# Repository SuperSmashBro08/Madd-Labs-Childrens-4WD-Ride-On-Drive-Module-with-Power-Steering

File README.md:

# Kids Ride-On Framework

An open-source framework for building smart, connected kids' ride-on vehicles with OTA (Over-The-Air) firmware updates, web-based control, and modular peripheral support.

---

## 🎯 Project Overview

This project provides a complete hardware and software framework for upgrading kids' electric ride-on toys with:

- **Dual-MCU Architecture**: ESP32-S3 for WiFi/Web + Teensy 4.1 for real-time control
- **OTA Firmware Updates**: Update both MCUs wirelessly via web browser
- **Web Dashboard**: Monitor and control the vehicle from any device
- **Modular Design**: Easy to add motors, LEDs, sensors, and more
- **Custom PCB**: Purpose-built circuit board for clean integration

---

## 📁 Project Structure

```
Kids-Ride-On-Framework/
├── esp32_flasher/           # ESP32-S3 firmware (WiFi, Web Server, OTA)
│   ├── esp32_flasher.ino    # Main ESP32 code
│   ├── secrets.h.example    # Template for WiFi credentials
│   └── README.md            # ESP32-specific documentation
│
├── teensy_flasherx/         # Teensy 4.1 firmware (Motor control, sensors)
│   ├── teensy_flasherx.ino  # Main application code (YOUR CODE HERE)
│   ├── FlasherXOTA.h/cpp    # OTA update handler (don't modify)
│   ├── FXUtil.h/cpp         # Intel HEX parser (don't modify)
│   ├── FlashTxx.h/c         # Flash primitives (don't modify)
│   └── README.md            # Teensy-specific documentation
│
├── hardware/                # Hardware design files
│   └── PCB/
│       └── Kids Ride On 2.1/
│           ├── Kicad files/ # KiCad schematic and PCB
│           ├── bom/         # Bill of materials
│           ├── 3d/          # 3D models
│           └── Production/  # Gerber files for manufacturing
│
├── Backup/                  # Backup of original firmware
├── readme files/            # Additional documentation
├── .gitignore               # Git ignore rules
└── README.md                # This file
```

---

## 🚀 Getting Started

### Prerequisites

- [Arduino IDE 2.x](https://www.arduino.cc/en/software) or [PlatformIO](https://platformio.org/)
- [Teensyduino](https://www.pjrc.com/teensy/teensyduino.html) add-on for Arduino IDE
- ESP32 Arduino Core (install via Board Manager)

### Hardware Required

- ESP32-S3 DevKitC (or compatible)
- Teensy 4.1
- Custom PCB (see `hardware/PCB/`) or breadboard setup
- 12V/24V power supply (depending on your motors)
- Motors, sensors, LEDs as needed

### Quick Start

1. **Clone the repository**
   ```bash
   git clone https://github.com/yourusername/kids-ride-on-framework.git
   cd kids-ride-on-framework
   ```

2. **Configure WiFi credentials**
   ```bash
   cd esp32_flasher
   cp secrets.h.example secrets.h
   # Edit secrets.h with your WiFi SSID and password
   ```

3. **Upload ESP32 firmware**
   - Open `esp32_flasher/esp32_flasher.ino` in Arduino IDE
   - Select board: ESP32-S3 Dev Module
   - Upload via USB
   - Open Serial Monitor to see the assigned IP address

4. **Upload Teensy firmware**
   - Open `teensy_flasherx/teensy_flasherx.ino` in Arduino IDE
   - Select board: Teensy 4.1
   - Upload via USB (first time only - then use OTA!)

5. **Access the Web Dashboard**
   - Open your browser to the IP address shown in Serial Monitor
   - You can now upload firmware updates wirelessly!

---

## ⚙️ Configuration

### Sensor Calibration (IMPORTANT!)

Every vehicle will have different sensor ranges. Open `teensy_flasherx/teensy_flasherx.ino` and find the **USER CONFIGURATION SECTION** near the top:

```cpp
//******************************************************************************
//                    USER CONFIGURATION SECTION
//******************************************************************************

// ----- STEERING 1 (Primary/Front) -----
#define STEERING1_PIN         A0      // Analog input pin
#define STEERING1_MIN         0       // Raw ADC at full LEFT
#define STEERING1_MAX         1023    // Raw ADC at full RIGHT
#define STEERING1_CENTER      512     // Raw ADC at CENTER

// ----- THROTTLE 1 (Primary) -----
#define THROTTLE1_PIN         A2      // Analog input pin
#define THROTTLE1_MIN         100     // Raw ADC at NO throttle
#define THROTTLE1_MAX         900     // Raw ADC at FULL throttle

// ... more configuration options
```

**How to calibrate:**
1. Upload the firmware with default values
2. Open Serial Monitor
3. Move your steering/throttle and note the raw ADC values
4. Update the MIN/MAX/CENTER values in the code
5. Re-upload (via OTA!)

### WiFi Configuration

For security, WiFi credentials are stored in `secrets.h` which is **not committed to git**.

1. Copy the example file:
   ```bash
   cp esp32_flasher/secrets.h.example esp32_flasher/secrets.h
   ```

2. Edit `secrets.h` with your credentials:
   ```cpp
   #define WIFI_SSID     "YourWiFiName"
   #define WIFI_PASSWORD "YourWiFiPassword"
   ```

---

## 🔧 Hardware

### PCB Design

The custom PCB connects the ESP32-S3 and Teensy 4.1 with proper level shifting and power regulation. Design files are in `hardware/PCB/Kids Ride On 2.1/`.

### Complete Pinout (V2.1 PCB)

#### Teensy 4.1 Pinout

**Analog Inputs (0–3.3V)**
| Pin | Function | Description |
|-----|----------|-------------|
| 17 (A3) | S1_WIPER | Steering Potentiometer |
| 23 (A9) | T1_WIPER | Throttle Potentiometer |
| 16 (A2) | AS5600_OUT | Magnetic Encoder Analog |
| 24 (A10) | STEER_I_L | Steering Motor Current Left |
| 25 (A11) | STEER_I_R | Steering Motor Current Right |
| 26 (A12) | FRONT_I_L | Front Drive Current Left |
| 27 (A13) | FRONT_I_R | Front Drive Current Right |
| 38 (A14) | REAR_I_L | Rear Drive Current Left |
| 39 (A15) | REAR_I_R | Rear Drive Current Right |

**Digital Inputs (3.3V Logic)**
| Pin | Function | Description |
|-----|----------|-------------|
| 28 | SHIFT_FWD | Shifter Forward |
| 29 | SHIFT_REV | Shifter Reverse |
| 30 | MODE_SEL | Mode Select |
| 31 | E_BRAKE | E-Brake Input |

**PWM Outputs (3.3V)**
| Pin | Function | Description |
|-----|----------|-------------|
| 2 | STEER_LPWM | Steering Left PWM |
| 3 | STEER_RPWM | Steering Right PWM |
| 6 | FRONT_LPWM | Front Drive Left PWM |
| 9 | FRONT_RPWM | Front Drive Right PWM |
| 12 | REAR_LPWM | Rear Drive Left PWM |
| 13 | REAR_RPWM | Rear Drive Right PWM |

**Motor Driver Enable (3.3V → 5V via level shifter)**
| Pin | Function | Description |
|-----|----------|-------------|
| 4 | STEER_L_EN | Steering Left Enable |
| 5 | STEER_R_EN | Steering Right Enable |
| 10 | FRONT_L_EN | Front Drive Left Enable |
| 11 | FRONT_R_EN | Front Drive Right Enable |
| 32 | REAR_L_EN | Rear Drive Left Enable |
| 33 | REAR_R_EN | Rear Drive Right Enable |

**I2C (AS5600 Encoder)**
| Pin | Function |
|-----|----------|
| 18 | SDA |
| 19 | SCL |

**UART to ESP32-S3**
| Teensy Pin | ESP32 Pin | Function |
|------------|-----------|----------|
| 7 (RX2) | GPIO43 (TX) | OTA Flash Data |
| 8 (TX2) | GPIO44 (RX) | OTA Flash Data |
| 14 (TX3) | GPIO18 (RX) | Debug Serial |
| 15 (RX3) | GPIO17 (TX) | Debug Serial |

#### ESP32-S3 Pinout

| GPIO | Function | Description |
|------|----------|-------------|
| 43 | UART TX | TX to Teensy RX2 (Pin 7) |
| 44 | UART RX | RX from Teensy TX2 (Pin 8) |
| 17 | UART TX | TX to Teensy RX3 (Pin 15) |
| 18 | UART RX | RX from Teensy TX3 (Pin 14) |
| 38 | RGB_LED | Status LED / Fiber Optic |

### Bill of Materials

See `hardware/PCB/Kids Ride On 2.1/bom/` for the complete parts list.

---

## 🌐 Web Interface

The ESP32 hosts a web server with:

- **System Status**: Connection status for both MCUs
- **Teensy OTA**: Upload `.hex` files to flash Teensy wirelessly
- **ESP32 OTA**: Upload `.bin` files to update ESP32 wirelessly
- **Serial Monitor**: Real-time serial output from both MCUs

Access via: `http://<ESP32-IP-ADDRESS>/`

---

## 📡 OTA Updates

### Updating Teensy

1. Compile your Teensy code in Arduino IDE
2. Find the `.hex` file in the build folder
3. Open the web dashboard
4. Drag & drop the `.hex` file onto "Flash Teensy 4.1"
5. Wait for completion - Teensy will reboot automatically

### Updating ESP32

1. Export compiled binary from Arduino IDE (Sketch → Export Compiled Binary)
2. Open the web dashboard
3. Drag & drop the `.bin` file onto "ESP32 OTA Update"
4. Wait for completion - ESP32 will reboot automatically

---

## 🛠️ Development

### Adding New Features

All your custom code goes in `teensy_flasherx/teensy_flasherx.ino`:

```cpp
void initPeripherals() {
    // Initialize your motors, LEDs, sensors here
}

void updatePeripherals() {
    // Your main control loop - runs every iteration
    // Read sensors, update motors, etc.
}
```

The FlasherX OTA code is encapsulated and doesn't need modification.

### File Overview

| File | Modify? | Purpose |
|------|---------|---------|
| `teensy_flasherx.ino` | ✅ YES | Your application code |
| `FlasherXOTA.h/cpp` | ❌ No | OTA update handler |
| `FXUtil.h/cpp` | ❌ No | Intel HEX parser |
| `FlashTxx.h/c` | ❌ No | Low-level flash access |
| `esp32_flasher.ino` | ⚠️ Rarely | Web server & OTA |

---

## 📋 Roadmap

- [x] OTA firmware updates for Teensy 4.1
- [x] OTA firmware updates for ESP32
- [x] Web-based dashboard
- [x] Serial monitor via WebSocket
- [ ] Motor control with acceleration ramping
- [ ] LED strip animations (NeoPixel/WS2812)
- [ ] Steering servo control
- [ ] Speed limiting / parental controls
- [ ] Bluetooth gamepad support
- [ ] Battery monitoring
- [ ] GPS tracking (optional)
- [ ] Mobile app

---

## 🤝 Contributing

Contributions are welcome! Please:

1. Fork the repository
2. Create a feature branch (`git checkout -b feature/amazing-feature`)
3. Commit your changes (`git commit -m 'Add amazing feature'`)
4. Push to the branch (`git push origin feature/amazing-feature`)
5. Open a Pull Request

---

## 📄 License

This project is open source and available under the [MIT License](LICENSE).

---

## ⚠️ Safety Warning

This project involves modifying children's toys with higher-powered electronics. Please:

- Always supervise children when using modified vehicles
- Install appropriate speed limiters
- Use proper fusing and circuit protection
- Test thoroughly in a safe environment
- Follow local regulations for motorized vehicles

---

## 🙏 Acknowledgments

- [FlasherX](https://github.com/joepasquariello/FlasherX) by Joe Pasquariello - Teensy OTA library
- [PJRC](https://www.pjrc.com/) - Teensy development
- [Espressif](https://www.espressif.com/) - ESP32 platform

---

**Happy Building! 🚗💨**

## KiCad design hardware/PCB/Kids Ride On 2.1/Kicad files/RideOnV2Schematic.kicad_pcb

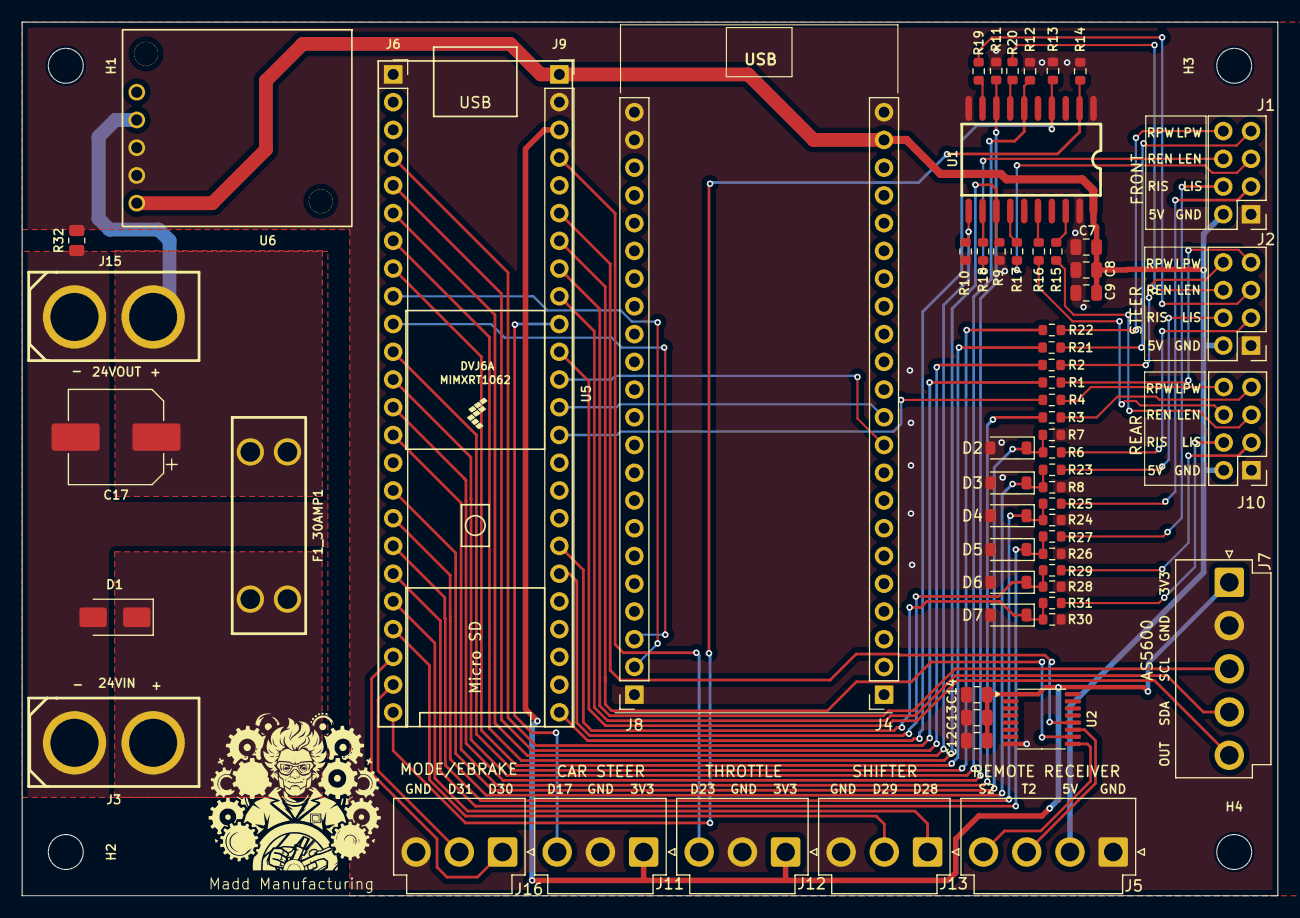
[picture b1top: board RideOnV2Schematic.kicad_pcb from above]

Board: 2 copper layers, 115.0 x 80.0 mm, 69 parts (0 on the bottom side), 65 nets.

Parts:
C7, C12: 100nF; C_0805_2012Metric
C8, C13: 1uF; C_0805_2012Metric
C9, C14: 10uF; C_0805_2012Metric
C17: 220uF/35V; CP_Elec_8x10.5
D1: SMAJ33A; D_SMA
D2, D3, D4, D5, D6, D7: 3.4V; D_SOD-123
F1_30AMP1: Fuse; FUSE-TH_4P-L19.8-W6.7_3557-2
H1, H2, H3, H4: MountingHole; MountingHole_3.2mm_M3
J1, J2, J10: Conn_02x04_Odd_Even; PinHeader_2x04_P2.54mm_Vertical
J3, J15: XT60-M.; CONN-TH_XT60
J4, J8: Conn_01x22; PinSocket_1x22_P2.54mm_Vertical
J5: Conn_01x04; JST_VH_B4P-VH-B_1x04_P3.96mm_Vertical
J6, J9: Conn_01x24; PinSocket_1x24_P2.54mm_Vertical
J7: Conn_01x05; JST_VH_B5P-VH-B_1x05_P3.96mm_Vertical
J11, J12, J13, J16: Conn_01x03; JST_VH_B3P-VH-B_1x03_P3.96mm_Vertical
R1, R2, R3, R4, R15, R16, R17, R18, R19, R20, R21, R22: 33R; R_0603_1608Metric
R6, R23, R25, R27, R29, R31: 1.8k; R_0603_1608Metric
R7, R8, R24, R26, R28, R30: 3.3k; R_0603_1608Metric
R9, R10, R11, R12, R13, R14: 10k; R_0603_1608Metric
R32: 0R; R_0805_2012Metric
U1: SN74AHCT244; SOIC-20_L12.8-W7.5-P1.27-LS10.3-BL
U2: CD74HC4050; TSSOP-16_4.4x5mm_P0.65mm
U5: Teensy4.1; Teensy41
U6: D24V50F5

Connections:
+3.3V: C12.1, C13.1, C14.1, J7.1, J9.3, J11.1, J12.1, U2.1 (VCC)
+5V: C7.1, C8.1, C9.1, J1.2, J2.2, J4.21, J5.2, J9.1, J10.2, U1.20 (VCC), U6.5 (VOUT)
+24V: C17.1, F1_30AMP1.1, J15.2, U6.2 (VIN)
/24VIN: D1.1 (A1), F1_30AMP1.2, J3.2
/FRONT_L_IS: J1.3, R25.2
/FRONT_R_IS: J1.4, R27.2
/OUT: J7.5, J9.11
/PIN_2: J6.4, R1.1
/PIN_3: J6.5, R2.1
/PIN_4: J6.6, R10.1, U1.11 (2A1)
/PIN_5: J6.7, R9.1, U1.13 (2A2)
/PIN_6: J6.8, R21.1
/PIN_7: J6.9, J8.2
/PIN_8: J6.10, J8.3
/PIN_9: J6.11, R22.1
/PIN_10: J6.12, R12.1, U1.6 (1A3)
/PIN_11: J6.13, R11.1, U1.8 (1A4)
/PIN_12: J6.14, R3.1
/PIN_13: J9.14, R4.1
/PIN_14: J4.11, J9.13
/PIN_15: J4.10, J9.12
/PIN_17: J9.10, J11.3
/PIN_18: J7.4, J9.9
/PIN_19: J7.3, J9.8
/PIN_20: J9.7, U2.10
/PIN_21: J9.6, U2.12
/PIN_23: J9.4, J12.3
/PIN_24: D2.1 (K), J6.16, R6.1, R7.2
/PIN_25: D3.1 (K), J6.17, R8.2, R23.1
/PIN_26: D4.1 (K), J6.18, R24.2, R25.1
/PIN_27: D5.1 (K), J6.19, R26.2, R27.1
/PIN_28: J6.20, J13.1
/PIN_29: J6.21, J13.2
/PIN_30: J6.22, J16.1
/PIN_31: J6.23, J16.2
/PIN_32: J6.24, R14.1, U1.2 (1A1)
/PIN_33: J9.24, R13.1, U1.4 (1A2)
/PIN_38: D6.1 (K), J9.19, R28.2, R29.1
/PIN_39: D7.1 (K), J9.18, R30.2, R31.1
/PIN_FRONT_LEN: J1.5, R17.2
/PIN_FRONT_LPWM: J1.7, R21.2
/PIN_FRONT_REN: J1.6, R18.2
/PIN_FRONT_RPWM: J1.8, R22.2
/PIN_REAR_LEN: J10.5, R15.2
/PIN_REAR_LPWM: J10.7, R3.2
/PIN_REAR_REN: J10.6, R16.2
/PIN_REAR_RPWM: J10.8, R4.2
/PIN_STEER_LEN: J2.5, R19.2
/PIN_STEER_LPWM: J2.7, R1.2
/PIN_STEER_REN: J2.6, R20.2
/PIN_STEER_RPWM: J2.8, R2.2
/REAR_L_IS: J10.3, R29.2
/REAR_R_IS: J10.4, R31.2
/S2: J5.4, U2.9
/STEER_L_IS: J2.3, R6.2
/STEER_R_IS: J2.4, R23.2
/T2: J5.3, U2.11
GND: C7.2, C8.2, C9.2, C12.2, C13.2, C14.2, D2.2 (A), D3.2 (A), D4.2 (A), D5.2 (A), D6.2 (A), D7.2 (A), J1.1, J2.1, J4.22, J5.1, J6.1, J7.2, J8.1, J8.21, J8.22, J9.2, J10.1, J11.2, J12.2, J13.3, J16.3, R7.1, R8.1, R9.2, R10.2, R11.2, R12.2, R13.2, R14.2, R24.1, R26.1, R28.1, R30.1, R32.2, U1.1 (1OE), U1.10 (GND), U1.19 (2OE), U2.8 (GND), U6.3 (GND1), U6.4 (GND2)
GNDPWR: C17.2, D1.2 (A2), J3.1, J15.1, R32.1
unnamed: R15.1, U1.18 (1Y1)
unnamed: R16.1, U1.16 (1Y2)
unnamed: R17.1, U1.14 (1Y3)
unnamed: R18.1, U1.12 (1Y4)
unnamed: R19.1, U1.9 (2Y1)
unnamed: R20.1, U1.7 (2Y2)

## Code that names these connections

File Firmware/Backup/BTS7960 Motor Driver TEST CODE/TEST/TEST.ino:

/*******************************************************************************
 * Teensy 4.1 Motor Driver Test - V2.1 PCB
 * 
 * Tests all 3 motor drivers (Steering, Front, Rear) together
 * Throttle pot = motor speed (0-100%)
 * Shifter = direction (FWD / REV / NEUTRAL)
 * 
 * Pure Teensy code - NO OTA, NO I2C, NO Telemetry
 ******************************************************************************/

#include <Arduino.h>

//====== PIN DEFINITIONS ======

// Throttle input
#define PIN_THROTTLE 23

// Shifter inputs (active LOW)
#define PIN_FWD 29
#define PIN_REV 28

// Steering motor
#define PIN_STEER_LPWM 2
#define PIN_STEER_RPWM 3
#define PIN_STEER_L_EN 4
#define PIN_STEER_R_EN 5

// Front motor
#define PIN_FRONT_LPWM 6
#define PIN_FRONT_RPWM 9
#define PIN_FRONT_L_EN 10
#define PIN_FRONT_R_EN 11

// Rear motor
#define PIN_REAR_LPWM 12
#define PIN_REAR_RPWM 13
#define PIN_REAR_L_EN 32
#define PIN_REAR_R_EN 33

//====== THROTTLE CALIBRATION ======
#define THROTTLE_MIN 249
#define THROTTLE_MAX 790
#define THROTTLE_DEADZONE 30

//====== SETUP ======
void setup() {
    Serial.begin(115200);
    delay(1000);
    
    Serial.println("\n========================================");
    Serial.println("  MOTOR DRIVER TEST - Teensy 4.1");
    Serial.println("========================================");
    Serial.println("3 Motors: Steering, Front, Rear");
    Serial.println("Throttle = Speed (0-100%)");
    Serial.println("Shifter = Direction (FWD/REV/NEUTRAL)");
    Serial.println();
    
    // Configure shifter inputs
    pinMode(PIN_FWD, INPUT_PULLUP);
    pinMode(PIN_REV, INPUT_PULLUP);
    
    // Configure all enable pins
    pinMode(PIN_STEER_L_EN, OUTPUT);
    pinMode(PIN_STEER_R_EN, OUTPUT);
    pinMode(PIN_FRONT_L_EN, OUTPUT);
    pinMode(PIN_FRONT_R_EN, OUTPUT);
    pinMode(PIN_REAR_L_EN, OUTPUT);
    pinMode(PIN_REAR_R_EN, OUTPUT);
    
    // Configure all PWM pins
    pinMode(PIN_STEER_LPWM, OUTPUT);
    pinMode(PIN_STEER_RPWM, OUTPUT);
    pinMode(PIN_FRONT_LPWM, OUTPUT);
    pinMode(PIN_FRONT_RPWM, OUTPUT);
    pinMode(PIN_REAR_LPWM, OUTPUT);
    pinMode(PIN_REAR_RPWM, OUTPUT);
    
    // Set PWM frequency
    analogWriteFrequency(PIN_STEER_LPWM, 20000);
    analogWriteFrequency(PIN_STEER_RPWM, 20000);
    analogWriteFrequency(PIN_FRONT_LPWM, 20000);
    analogWriteFrequency(PIN_FRONT_RPWM, 20000);
    analogWriteFrequency(PIN_REAR_LPWM, 20000);
    analogWriteFrequency(PIN_REAR_RPWM, 20000);
    
    // All motors off initially
    allMotorsOff();
    
    Serial.println("Ready. Move throttle and shifter to test...\n");
}

//====== MAIN LOOP ======
void loop() {
    // Read throttle
    int throttleRaw = analogRead(PIN_THROTTLE);
    int throttlePercent = 0;
    
    if (throttleRaw > THROTTLE_MIN + THROTTLE_DEADZONE) {
        throttlePercent = map(throttleRaw, 
                              THROTTLE_MIN + THROTTLE_DEADZONE,
                              THROTTLE_MAX, 
                              0, 100);
        throttlePercent = constrain(throttlePercent, 0, 100);
    }
    
    // Convert to PWM (0-255)
    int pwmValue = map(throttlePercent, 0, 100, 0, 255);
    
    // Read shifter (active LOW)
    bool isFwd = (digitalRead(PIN_FWD) == LOW);
    bool isRev = (digitalRead(PIN_REV) == LOW);
    
    // Determine gear
    int gear = 0;  // 0=NEUTRAL, 1=FORWARD, 2=REVERSE
    if (isFwd) gear = 1;
    else if (isRev) gear = 2;
    
    // Apply motor control
    driveAllMotors(gear, pwmValue);
    
    // Print every 200ms
    static unsigned long lastPrint = 0;
    if (millis() - lastPrint >= 200) {
        lastPrint = millis();
        
        const char* gearStr = (gear == 1) ? "FWD" : (gear == 2) ? "REV" : "NEU";
        Serial.printf("Throttle: %3d%% (raw=%3d) | PWM: %3d | Gear: %s | FWD_pin: %d | REV_pin: %d | EN_pins: L_EN=%d R_EN=%d\n",
                     throttlePercent, throttleRaw, pwmValue, gearStr,
                     digitalRead(PIN_FWD), digitalRead(PIN_REV),
                     digitalRead(PIN_STEER_L_EN), digitalRead(PIN_STEER_R_EN));
    }
}

//====== DRIVE ALL MOTORS ======
void driveAllMotors(int gear, int pwmValue) {
    // Enable all drivers
    digitalWrite(PIN_STEER_L_EN, HIGH);
    digitalWrite(PIN_STEER_R_EN, HIGH);
    digitalWrite(PIN_FRONT_L_EN, HIGH);
    digitalWrite(PIN_FRONT_R_EN, HIGH);
    digitalWrite(PIN_REAR_L_EN, HIGH);
    digitalWrite(PIN_REAR_R_EN, HIGH);
    
    if (pwmValue == 0) {
        // No throttle - all off
        allMotorsOff();
    } 
    else if (gear == 1) {
        // FORWARD - apply to L_PWM pins
        analogWrite(PIN_STEER_LPWM, pwmValue);
        analogWrite(PIN_STEER_RPWM, 0);
        analogWrite(PIN_FRONT_LPWM, pwmValue);
        analogWrite(PIN_FRONT_RPWM, 0);
        analogWrite(PIN_REAR_LPWM, pwmValue);
        analogWrite(PIN_REAR_RPWM, 0);
    } 
    else if (gear == 2) {
        // REVERSE - apply to R_PWM pins
        analogWrite(PIN_STEER_LPWM, 0);
        analogWrite(PIN_STEER_RPWM, pwmValue);
        analogWrite(PIN_FRONT_LPWM, 0);
        analogWrite(PIN_FRONT_RPWM, pwmValue);
        analogWrite(PIN_REAR_LPWM, 0);
        analogWrite(PIN_REAR_RPWM, pwmValue);
    } 
    else {
        // NEUTRAL - all off
        allMotorsOff();
    }
}

//====== ALL MOTORS OFF ======
void allMotorsOff() {
    analogWrite(PIN_STEER_LPWM, 0);
    analogWrite(PIN_STEER_RPWM, 0);
    analogWrite(PIN_FRONT_LPWM, 0);
    analogWrite(PIN_FRONT_RPWM, 0);
    analogWrite(PIN_REAR_LPWM, 0);
    analogWrite(PIN_REAR_RPWM, 0);
}

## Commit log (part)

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2025-12-24 Initial commit: Kids Ride-On Framework v1.3.0 - ESP32-S3 + Teensy 4.1 OTA system with telemetry
2025-12-29 update101
2026-01-04 MAIN
2026-01-04 Main 2

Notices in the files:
README.md:
License: MIT
